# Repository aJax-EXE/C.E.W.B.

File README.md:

# C.E.W.B.: The Open Source Teaching Platform for Control Systems
**ECEN4620/MCEN4085: Senior Design Project - University of Colorado Boulder**  
**Sponsors:** Talles Santos  
&emsp;&emsp;&emsp;&emsp;&emsp; Nathan McNeil  
**Students:** [Alyssa Jackson](https://github.com/aJax-EXE) (Electrical and Computer Engineering)  
&emsp;&emsp;&emsp;&emsp;&emsp;Eric Pollert (Mechanical Engineering)  
&emsp;&emsp;&emsp;&emsp;&emsp;[Isaiah Knox](https://github.com/iknox001) (Mechanical Engineering)  

---

## Table of Contents
1. [Introduction](#introduction)
2. [Project Overview](#project-overview)
3. [System Specifications](#system-specifications)
4. [Repository Structure](#repository-structure)
5. [Hardware](#hardware)
   - [Circuit Design](#circuit-design)
   - [Data Transmission](#data-transmission)
   - [Accessory Storage](#accessory-storage)
   - [Device Deck](#device-deck)
   - [Motor Housing](#motor-housing)
   - [Electrical Compartment](#electrical-compartment)
   - [Attachments](#attachments)
6. [Software](#software)
   - [Dependencies](#dependencies)
   - [Arduino Code](#arduino-code)
   - [MATLAB/Simulink Interface](#matlabsimulink-interface)
   - [Custom Libraries](#custom-libraries)
7. [Getting Started](#getting-started)
   - [Hardware Setup](#hardware-setup)
   - [Software Setup](#software-setup)
   - [Running Your First Experiment](#running-your-first-experiment)
8. [Lab Experiments](#lab-experiments)
   - [Angular Position Control (Inertia Disc)](#angular-position-control-inertia-disc)
   - [Inverted Pendulum Balancing](#inverted-pendulum-balancing)
9. [Results](#results)
10. [Known Limitations](#known-limitations)
11. [Next Steps](#next-steps)
    - [List of Issues](#list-of-issues)
    - [After CEWB Functionality is Reached](#after-cewb-functionality-is-reached)
12. [Contributing](#contributing)
13. [License](#license)

---

*The CEWB, fully built*  
&emsp;

---

## Introduction

C.E.W.B. (name pending; referred to as 'CEWB' throughout this README) is a low-cost, open-source electromechanical teaching platform designed for teaching and applying control systems concepts in a real-world environment. It was developed as a direct functional replacement for the Quanser Qube-Servo 2, a $5,000 proprietary device that is now outdated and requires an older version of MATLAB to operate.

The device supports the same core laboratory experiments as the Qube-Servo 2, including angular position control with an inertia disc and inverted pendulum balancing. It is designed to be self-contained, portable, and fully compatible with MATLAB and Simulink.

All design files, code, and documentation are publicly available in this repository so that the device can be reproduced by any institution without reliance on proprietary hardware or software.

---

## Project Overview

This project set out to design a low-cost, open-source replacement for the Quanser Qube-Servo 2, a $5,000 device used in control systems classes. The target was a fully functional prototype delivered by May 2026 at under $1,000 per unit, capable of supporting the same lab experiments — including angular position control with an inertia disc and inverted pendulum balancing — while being self-contained, portable, and compatible with MATLAB/Simulink.

The design integrates all components into a Nanuk 905 protective case with built-in storage for attachments, cables, and the power supply. The system uses an Arduino microcontroller, a motor driver, and a custom PCB, with two interchangeable magnetic attachments — an inertia disc and a pendulum — mirroring the Qube-Servo 2's functionality. The projected per-unit production cost of $763.68 comes in well under the $1,000 target.

The device met most implementation requirements. Data transmission, MATLAB/Simulink compatibility, third-party manufacturability, self-contained storage, and transport protection all passed evaluation. Open-source documentation, including CAD files, a bill of materials, and assembly instructions, has been prepared and made publicly available.

However, the device did not fully replicate the closed-loop control performance of the Qube-Servo 2. The Arduino's data transmission rate is approximately an order of magnitude slower than the proprietary controller used in the Qube-Servo 2, causing significant control loop delays and excessive overshoot during inertia disc testing. As a result, the pendulum balancing test was not attempted.

The primary recommended next step is to replace the Arduino with a faster microcontroller, retest the system using the same control experiments, and proceed to a small production run once performance requirements are confirmed to be met.

---

## System Specifications

The following table lists the key performance parameters of the C.E.W.B. system alongside the Qube-Servo 2 equivalents for reference.

| Parameter | C.E.W.B. | Qube-Servo 2 |
|---|---|---|
| Motor | Maxon DC-max 26 S Ø26 mm | Maxon (discontinued) |
| Nominal input voltage | 24 V | 18 V |
| Nominal torque | 22.0 mN-m | 22.0 mN-m |
| Nominal speed | 3050 RPM | 3050 RPM |
| Encoder line count | 512 lines/rev | 512 lines/rev |
| Encoder resolution (quadrature) | 2048 counts/rev | 2048 counts/rev |
| Encoder resolution (deg) | 0.176 deg/count | 0.176 deg/count |
| Encoder resolution (rad) | 0.00307 rad/count | 0.00307 rad/count |
| Motor controller | Adafruit DRV8871 | PWM amplifier |
| Microcontroller | Arduino Uno R3 | Proprietary |
| Data transmission rate | ~50 Hz (USB serial) | ~500 Hz (proprietary) |
| Output voltage range | ±24 V | ±10 V (recommended) |
| Per-unit cost (production) | $763.68 | $5,000.00 |

---

## Repository Structure

```
C.E.W.B./
├── Datasheets/
│   ├── Electrical/                                # Datasheets for all electrical components
│   └── Hardware/                                  # Datasheets for hardware components
├── Documentation/                                # Documentation from the Senior Projects Class
├── Hardware/
│   ├── 3DModels/
│   │   ├── CurrentVersion/                       # Final production CAD files (SolidWorks)
│   │   │   ├── Device Components/                # All structural device parts
│   │   │   │   ├── Full Assembly.SLDASM
│   │   │   │   ├── Motor Arm.SLDASM
│   │   │   │   ├── Housing.SLDPRT
│   │   │   │   ├── Motor Plate.SLDPRT
│   │   │   │   ├── Motor Leg.SLDPRT
│   │   │   │   ├── Plate bend inlet.SLDPRT
│   │   │   │   ├── Inertia Disc.SLDPRT
│   │   │   │   ├── Attachment Interface.SLDPRT
│   │   │   │   ├── Pendulum Assembly.SLDASM
│   │   │   │   ├── Pendulum mount.SLDPRT
│   │   │   │   ├── Pendulum shaft.SLDPRT
│   │   │   │   ├── Pendulum Arm.SLDPRT
│   │   │   │   ├── Pendulum Stop.SLDPRT
│   │   │   │   ├── PCB.SLDPRT
│   │   │   │   ├── PCB Mounting Plate.SLDPRT
│   │   │   │   └── [purchased hardware SLDPRTs]
│   │   │   └── Storage Compartment Components/   # Lid storage assembly parts
│   │   │       ├── Foam_Panel.SLDPRT
│   │   │       ├── Front Panel.SLDPRT
│   │   │       └── Rear Lid Panel.SLDPRT
│   │   └── PastVersions/                         # Design iteration history
│   └── PCBModels/
│       ├── ArduinoShieldDesign/                  # KiCad PCB design files
│       │   ├── ForwardDesign/                    # Current production PCB
│       │   ├── ReverseDesign/                    # Earlier PCB iteration
│       │   ├── OldTestBoard/                     # First test board
│       │   └── PotentialFix/                     # Proposed PCB fix iteration
│       ├── GerberFiles/
│       │   ├── ForwardFiles/                     # Gerber files for production PCB
│           └── ReverseFiles/                     # Gerber files for reverse design
├── Images/                                       # Images used in this README and in the documentation
├── Software/
│   ├── Libraries/                                # Arduino libraries — install these manually
│   │   ├── CombiningEncoderCounts/               # CEWBEncoder source
│   │   │   ├── CEWBEncoder.cpp
│   │   │   └── CEWBEncoder.h
│   │   └── OtherFunctions/                       # CEWBFunctions source
│   │       ├── CEWBFunctions.cpp
│   │       └── CEWBFunctions.h
│   ├── ExamplesAndTests/
│   │   ├── ArduinoTests/                         # Standalone Arduino diagnostic sketches
│   │   │   ├── CalcToAnalogVal/                  # PWM value calculator
│   │   │   ├── CommunicationConstantlySendingData/  # Serial format test
│   │   │   ├── EncoderQuadTest/                  # Encoder wiring verification
│   │   │   ├── InterruptEncoderTest/             # Interrupt-based encoder test
│   │   │   └── MotorRampSpeedTest/               # Motor driver verification
│   │   ├── ProofOfConcept/                       # Early proof-of-concept scripts
│   │   └── SimulinkTests/                        # Simulink integration test models
│   │       ├── BasicSimulinkCommunication/       # Initial serial block example
│   │       ├── BypassSerialBlockSimulinkConnectionTest/
│   │       ├── CompleteSimulinkRunTest/
│   │       │   ├── BasicRunning/                 # Open-loop voltage test model
│   │       │   └── WorkingModel/                 # ⭐ Main working model
│   │       │       ├── ArduinoSerial.m           # MATLAB System block
│   │       │       ├── WorkingModel.ino          # Arduino sketch
│   │       │       └── PIDController.slx         # Simulink model
│   │       ├── SimulinkFormattingTest/
│   │       └── SimulinkReadEncoder/              # Encoder-only read test
│   ├── SendingBytesTest/                         # Binary byte transmission experiment
│   ├── SimulinkReadWriteSerialPort/              # Early serial block experiments
│   ├── SpinMotorWithSimulinkTest/                # Motor spin test
│   └── UpgradedMotorWSimulinkTest/               # Updated motor test
├── .gitignore
└── README.md
```
 
> ⭐ **For most users, the only files needed are in `Software/ExamplesAndTests/SimulinkTests/CompleteSimulinkRunTest/WorkingModel/`** — the Arduino sketch, MATLAB System block, and Simulink model are all there.
---

## Hardware

&emsp;
  
*3D models of the CEWB and its parts*  
&emsp;

### Circuit Design

*The CEWB electrical schematic*  
&emsp;

*The CEWB PCB model*  
&emsp;

The electrical system is built around an Arduino Uno R3 microcontroller and an Adafruit DRV8871 motor driver, both connected through a custom PCB. The PCB acts as a junction point between the motor, encoders, and microcontroller, consolidating all wiring and reducing the risk of loose connections. A 24V Mean Well GST90A24-P1M power supply provides power to the system via a front-panel power port. A front-panel USB-B port connects the Arduino to the user's laptop for data transmission.

The PCB is insulated from the aluminum mounting panel using an acrylic backing plate to prevent electrical interference.

### Data Transmission

Communication between the Arduino and MATLAB/Simulink is handled over USB serial at 115200 baud using a custom request/response packet protocol. Simulink sends a scaled integer voltage command, and the Arduino responds with the current encoder count and applied voltage. The full protocol is described in the [Arduino Code](#arduino-code) section of the Software documentation.

### Accessory Storage

*The storage lid that houses the CEWB attachments*  
&emsp;

The accessory storage compartment is made up of two pieces of hardboard and one piece of foam with cutouts for the accessories to fit into. The rear panel of hardboard has magnets glued into it, which allow the attachments to be secured in their respective locations during storage. Hardboard was selected for the front and rear panels as it is a light, cheap, and sturdy material. Foam was chosen for the middle panel as it is low-density and fills the space between the boards without significantly increasing weight. The three panels are glued together with super glue and are fixed into the top of the Nanuk 905 case using thread-forming screws.

### Device Deck

The main part of the deck of the device is a bent piece of aluminum sheet metal which is screwed into the Nanuk 905 case using thread-forming screws and serves as a mounting plate for the rest of the components. This part is bent to create a compartment for storing the power supply and the data transmission cable. The top surface of this panel has two ports: a USB port where the data transmission cable is plugged in, and a power port where the device is connected to the power supply. The ports were added to clean up the visual appearance of the device and remove the need for cables to be plugged directly into the electrical compartment. On the right side of the panel there is a cavity with a U-shaped bent piece of aluminum sheet metal mounted to the bottom of the panel, which serves both as a mounting location for the motor housing and as a barrier between the user and the internal components. The cavity allows the motor housing to fold into the device when stored. The trough contains a hole to allow wires to pass through between the motor housing and the electrical compartment. This hole is lined with a silicone grommet which protects the wires from fraying when the motor housing is moved between its storage and operating positions.

### Motor Housing

The motor housing consists of three main structural components, all made from aluminum sheet metal. The two motor housing legs give the housing the height required for the pendulum attachment and serve as the mounting location for the hinge, which allows the housing to pivot between its operational and storage positions. The hinge consists of a partially threaded socket head screw, nuts, and nylon washers. The partially threaded screw was chosen to provide a smooth surface for the hinge to rotate on. The nylon washers secure the housing in place during operation while still allowing rotation under sufficient force to slightly deform the nylon. The two washers at the end are jammed together to secure the hinge at a calibrated tightness, ensuring the hinge can be rotated but remains secured during operation.

The third structural component is the motor mounting plate, which features a bend that serves as a handle when switching the device between positions. This plate is attached at the top of the two motor legs using bolts and locknuts, and has the motor mounted to its underside using machine screws secured directly into threaded holes in the top of the motor. The motor is from Maxon and was chosen to replicate the motor of the Qube-Servo 2 as closely as possible given that the original motor is no longer available. An optical encoder is mounted to the rear axle of the motor using double-sided adhesive, which allows the encoder to be secured firmly without screws, as there are no mounting locations on the rear of the motor. The attachment interface is a small machined aluminum disc mounted to the end of the top motor shaft using a set screw. This component has magnets that allow the attachments to be fixed to the motor shaft during use. The motor plate also has a small 3D-printed elbow-shaped component mounted near the motor, which serves as a stop to prevent the pendulum from over-rotating and damaging its wiring. The mounting plate also has a 3.5 mm jack port for connecting the encoder from the pendulum attachment during use.

### Electrical Compartment

*The CEWB electrical compartment*  
&emsp;

The electrical compartment is located between the bend in the top panel of the device deck and the trough. The electrical components — including the motor driver, Arduino, and PCB — are mounted to the backside of the panel using nuts and bolts, with a piece of acrylic sized to match the PCB placed behind it to insulate the exposed circuitry from the aluminum panel and prevent electrical interference.

### Attachments

The two attachments are the inertia disc and the pendulum. The inertia disc is a machined aluminum disc which adds rotational inertia to the motor shaft for use in position control experiments. The disc has lines engraved into its top surface which allow the user to visually track the motor's position and verify control system behavior. The disc has four magnets on the back which allow it to be secured to the attachment interface during use and to the attachment storage compartment when stored.

The pendulum consists of three machined components. The pendulum cylinder is machined from aluminum and is the mounting location for the pendulum assembly. It has magnets on one side for mounting to the attachment interface and storage compartment, and two bearings press-fit into its internal bore which allow the pendulum axle to rotate freely. The pendulum axle is made from steel and is inserted through the two bearings and secured using two retaining rings that fit into grooves in the axle positioned to press against the bearings. An optical encoder is attached to the pendulum cylinder using machine screws and tracks the angular position of the axle during pendulum experiments. The encoder connects via a 3.5 mm cable to a jack on the motor mounting plate, allowing encoder data to be transmitted to the electrical compartment. The pendulum arm is mounted on the far end of the axle using a set screw and acts as a counterweight to create the tipping moment that the control system must compensate for in the inverted pendulum experiment.

---

## Software

### Dependencies

**Arduino IDE (1.8.x recommended)**
- CEWBEncoder (included in `Software/MATLAB/Libraries/CEWBEncoder/`)
- CEWBFunctions (included in `Software/MATLAB/Libraries/CEWBFunctions/`)

**MATLAB/Simulink**
- MATLAB R2024b or later
- Simulink
- No additional toolboxes required — serial communication is handled via a custom `matlab.System` object

### Arduino Code

The main Arduino sketch (`WorkingModel.ino`) implements a simple request/response serial protocol. Simulink sends a voltage command, the Arduino executes it on the motor, and responds with the current encoder count and applied voltage.

**Packet format:**

| Direction | Format | Example |
|---|---|---|
| Simulink → Arduino | `#sXXXXXX\n` | `#+037500\n` (3.75V × 10000) |
| Arduino → Simulink | `#sXXXXXX,sXXXXXX\n` | `#+000512,+037500\n` |

Voltage is transmitted as a scaled integer (real volts × 10000) to preserve 4 decimal places without transmitting a decimal point. Conversion is handled by `makeVoltage()` in CEWBFunctions.

The Arduino also implements a **500ms watchdog** — if no packet is received within 500ms (e.g. if Simulink is stopped or the USB cable is disconnected), the motor is cut automatically.

### MATLAB/Simulink Interface

Communication between Simulink and the Arduino is handled by `ArduinoSerial.m`, a `matlab.System` subclass that runs a 200Hz background timer independently of the Simulink step rate. This decouples serial timing from Simulink's solver, allowing smoother encoder data with less blocking.

**Block interface:**

| Port | Direction | Description |
|---|---|---|
| `v_in` | Input | Voltage command (−6 to +6 V) |
| `enc_out` | Output | Raw encoder count |
| `v_out` | Output | Voltage currently applied (for scope) |

**Configurable block parameters (set by double-clicking the block):**

| Parameter | Default | Description |
|---|---|---|
| `COMPort` | `/dev/ttyACM0` | Serial port (Linux) or `COM3` (Windows) |
| `BaudRate` | `115200` | Serial baud rate |
| `TimerPeriod` | `0.005` | Background timer period in seconds (0.005 = 200Hz) |

To convert `enc_out` to angle, wire it through a Gain block set to `(2*pi)/2048` for radians or `360/2048` for degrees.

### Custom Libraries

**CEWBEncoder**  
Interrupt-driven quadrature encoder library supporting ENC1X, ENC2X, and ENC4X decoding modes using Arduino pin change interrupts (PCINT). Supports up to 8 encoders simultaneously.

Key functions:
```cpp
CEWBEncoder enc(pinA, pinB, ENC4X);  // constructor
enc.begin();                          // enable interrupts
enc.getCount();                       // returns long count
enc.getDirection();                   // returns -1, 0, or 1
enc.resetCount();                     // resets count to zero
```

**CEWBFunctions**  
Utility functions for motor voltage conversion.

Key functions:
```cpp
voltToPWM(float voltage);   // converts voltage magnitude to PWM (0-255)
PWMToVolt(uint8_t PWM);     // converts PWM back to voltage
makeVoltage(long value);    // descales integer (value / 10000.0) to float volts
```

Note: `voltToPWM` maps voltage against a 24V maximum (`maxVolt = 24`). Passing values above 24V returns 255. Always pass `fabsf(voltage)` — direction is handled separately by `spinMotor`.

---

## Getting Started

### Hardware Setup

1. Connect the USB-B cable from the device's front panel USB port to your laptop.
2. Connect the power cable to the device's front panel power port and plug it into the wall.
3. Raise the motor housing to its upright operating position.
4. Attach the desired attachment (inertia disc or pendulum) to the motor interface magnetically.
5. If using the pendulum attachment, plug the 3.5 mm encoder cable into the jack on the motor plate.

> ⚠️ **Before use, ensure the motor housing is in the upright position and that power and computer cables — along with any other objects — are clear of the motor shaft.**

### Software Setup

**Arduino:**
1. Install Arduino IDE 1.8.x.
2. Copy `CEWBEncoder` and `CEWBFunctions` folders from `Software/MATLAB/Libraries/` into your Arduino libraries directory:
   - Linux (Snap): `~/snap/arduino/85/Arduino/libraries/`
   - Linux (AppImage/standard): `~/Arduino/libraries/`
   - Windows: `Documents/Arduino/libraries/`
3. Open `Software/Arduino/WorkingModel/WorkingModel.ino` in Arduino IDE.
4. Select **Tools → Board → Arduino Uno** and the correct port under **Tools → Port**.
5. Upload the sketch.

**MATLAB/Simulink:**
1. Place `ArduinoSerial.m` in the same folder as your Simulink `.slx` model file — Simulink looks for it by name in the current working directory.
2. Open your Simulink model.
3. Add a **MATLAB System** block (Simulink → User-Defined Functions → MATLAB System).
4. Double-click the block and select `ArduinoSerial` from the dropdown.

> ⚠️ **If `ArduinoSerial` does not appear in the dropdown, the `.m` file is not in the same folder as your Simulink model. Move it and try again.**

5. Set `COMPort` to match your Arduino's port (check Arduino IDE → Tools → Port).
6. Set the Simulink solver to **Fixed-step**, step size `0.02` (Ctrl+E → Solver).
7. Press **Play** — the block handles serial port opening, the background timer, and cleanup automatically.

### Running Your First Experiment

*The block diagram of the first example experiment*  
&emsp;

A simple open-loop voltage test:
1. Add a **Signal Generator** block (square wave, amplitude 3, frequency 0.5 Hz).
2. Wire it to `v_in` on the ArduinoSerial block.
3. Add a **Gain** block after `enc_out` with value `360/2048` to convert counts to degrees.
4. Connect both the Gain output and `v_out` to a **Scope** block.
5. Press **Play**. The motor should respond to the square wave and the scope should display the angular position and applied voltage.

---

## Lab Experiments

### Angular Position Control (Inertia Disc)

**Objective:** Command the inertia disc to move between angular positions (e.g. +1 rad and −1 rad) while minimizing overshoot using a PID controller.

**Simulink wiring:**
```
Constant (setpoint, rad) ──► Sum(+−) ──► PID ──► Saturation(±6V) ──► v_in ──► ArduinoSerial
                                ▲                                                      │
                                └──────────── Gain(2π/2048) ◄──── enc_out ────────────┘
```

**Recommended starting PID gains:**

| Gain | Starting Value |
|---|---|
| Kp | 0.1 |
| Ki | 0.0 |
| Kd | 0.1 (use filtered derivative: `10s/(s+10)`) |

> **Important:** Do not use Simulink's built-in `Derivative` block — it has infinite gain at high frequencies and will amplify serial timing noise, causing unstable motor behavior. Use a `Transfer Fcn` block with numerator `[10 0]` and denominator `[1 10]` instead.

**Note:** Due to the Arduino's ~20ms serial round-trip latency, aggressive PID gains will cause instability. Start with a low Kp and no derivative term, then increase gradually.

### Inverted Pendulum Balancing

> **Status: Not yet validated.** The inverted pendulum experiment requires faster closed-loop performance than the current Arduino-based system can reliably provide. This experiment is planned for a future hardware revision using a faster microcontroller. See [Next Steps](#next-steps).

---

## Results

The device met the following design requirements:

| Requirement | Target | Result |
|---|---|---|
| Accurate data transmission | Pass | ✅ Pass |
| MATLAB/Simulink compatibility | Pass | ✅ Pass |
| Cost target | < $1,000 | ✅ $763.68 |
| Self-contained storage | Pass | ✅ Pass |
| Transport protection | Pass | ✅ Pass (Nanuk 905, ASTM D-4169 DC-18 certified) |
| Third-party manufacturability | Pass | ✅ Pass |
| Software updatability | Pass | ✅ Pass (on supported MATLAB versions) |
| Qube function replication | Pass | ❌ Partial — inertia disc overshoot; pendulum not attempted |
| Motor and encoder performance | Comparable | ❌ Not met under closed-loop conditions |

---

## Known Limitations
**Serial latency (~20ms round-trip)**  
The Arduino Uno communicates over USB serial at approximately 50Hz, compared to the Qube-Servo 2's ~500Hz proprietary interface. This introduces significant control loop delay, causing excessive overshoot at higher PID gains. The background timer in `ArduinoSerial.m` partially mitigates this by running at 200Hz independently of Simulink, but the underlying serial round-trip remains the bottleneck.

**Encoder noise at high motor speeds**  
At high voltages, motor vibration can introduce noise on the encoder signal lines, causing occasional miscounts. Adding 10–100nF ceramic capacitors between each encoder signal pin and GND reduces this significantly.

**`voltToPWM` maps against 24V maximum**  
The `voltToPWM` function in CEWBFunctions maps input voltage against a 24V maximum. Voltages in the recommended ±6V operating range use only 25% of the available PWM range. If finer motor resolution is needed, change `maxVolt` in `CEWBFunctions.cpp` to match your intended operating voltage range.

---

## Next Steps

### List of Issues

In order to address the fundamental limitations of the CEWB and improve it in future iterations, the following items should be investigated:

- **Research faster microcontrollers**  
  The Arduino Uno R3 is not powerful enough to spin the motor, count the encoder position, and transmit/receive data to and from Simulink accurately in real time. To improve throughput and reduce computational bottlenecks, consider:
  - Using a single faster microcontroller (Raspberry Pi Pico, STM32, Teensy 4.x, etc.)
  - Using two or more microcontrollers with divided responsibilities — e.g. one handling motor control and encoder counting while another manages data transmission

- **Switch data transmission from strings to bytes**  
  The current string-based packet format is human-readable and useful for debugging, but binary byte transmission is significantly faster. The string format should be retained as a diagnostic/test option, but the production firmware should use binary packets.

- **Research higher-rate data transmission methods**  
  The Arduino Uno communicates at approximately 50Hz while the Qube-Servo 2 operates at ~500Hz. Investigate how the Qube-Servo 2 achieves this rate and identify equivalent approaches for the CEWB.

- **Look into wireless encoders for the inverted pendulum**  
  With the current setup, the pendulum attachment cannot rotate continuously 360° because of the wire connecting to the audio jack port on the motor plate. While this is sufficient for balancing at 180°, a wireless encoder connection would eliminate the rotation constraint and enable more complex experiments.

- **Add a strap to secure the inverted pendulum attachment in storage**  
  Currently, the pendulum shaft falls out of its storage cutout and props the lid open, preventing it from closing. A simple retaining strap would resolve this without requiring significant redesign.

- **Develop additional inertia disc variants**  
  Additional discs of different masses and radii would provide a wider range of system dynamics, enriching the experiments that can be demonstrated and taught.

- **Combine the `CEWBEncoder` and `CEWBFunctions` libraries**  
  Consolidating both libraries into a single library would not improve performance but would simplify installation and make the codebase easier for users to navigate.

- **Refine 3D models**  
  Minor dimensional discrepancies have been observed in received parts. While all parts are functional, tighter tolerances and updated models would reduce the need for post-receipt modification.

- **Document fabrication vendors and order specifications**  
  For the project to scale to wider adoption, the specific vendors used and the exact order specifications (dimensions, material, finish, etc.) for each custom part should be documented in the repository.

- **Investigate current surge protection**  
  If the motor stalls, current can spike and potentially damage other electrical components. Additional protection circuitry beyond the motor driver's built-in limiting should be explored.

- **Finalize the C.E.W.B. name**  
  The name was conceived to copy the Qube's spelling but does not currently stand for anything. A meaningful acronym or a new name entirely should be decided upon before wider release.

- **Research ways to make the motor run quieter**  
    The motor constantly emits a low and piercing buzz that can cause headaches. Look into making that stop and run quiet like the Qube does.

### After CEWB Functionality is Reached

Once the CEWB achieves reliable closed-loop performance, the following steps are planned:
1. Retest angular position control with the inertia disc using the same PID experiments
2. Attempt and validate inverted pendulum balancing
3. Assemble a small production run for deployment in the control systems course
4. Provide a prototype unit to the course instructor for curriculum integration

---

## Contributing

This project is open-source and contributions are welcome. To contribute:

1. Fork the repository
2. Create a feature branch (`git checkout -b feature/your-feature`)
3. Commit your changes (`git commit -m 'Add your feature'`)
4. Push to the branch (`git push origin feature/your-feature`)
5. Open a pull request

For questions or technical support, contact:
- **Dr. Talles Santos** (project sponsor): Talles.Santos@colorado.edu
- **Dr. Nathan McNeil** (project sponsor): Nathan.Mcneil@colorado.edu
- **Alyssa Jackson** (project member): alyssajackson436@gmail.com
- **US Digital** (encoders): support@usdigital.com | 800-736-0194
- **Maxon Motors**: info.us@maxongroup.com | (508) 677-0520

---

## License

This project is open-source. All CAD files, code, and documentation are made publicly available for reproduction and modification. See the repository for license details.

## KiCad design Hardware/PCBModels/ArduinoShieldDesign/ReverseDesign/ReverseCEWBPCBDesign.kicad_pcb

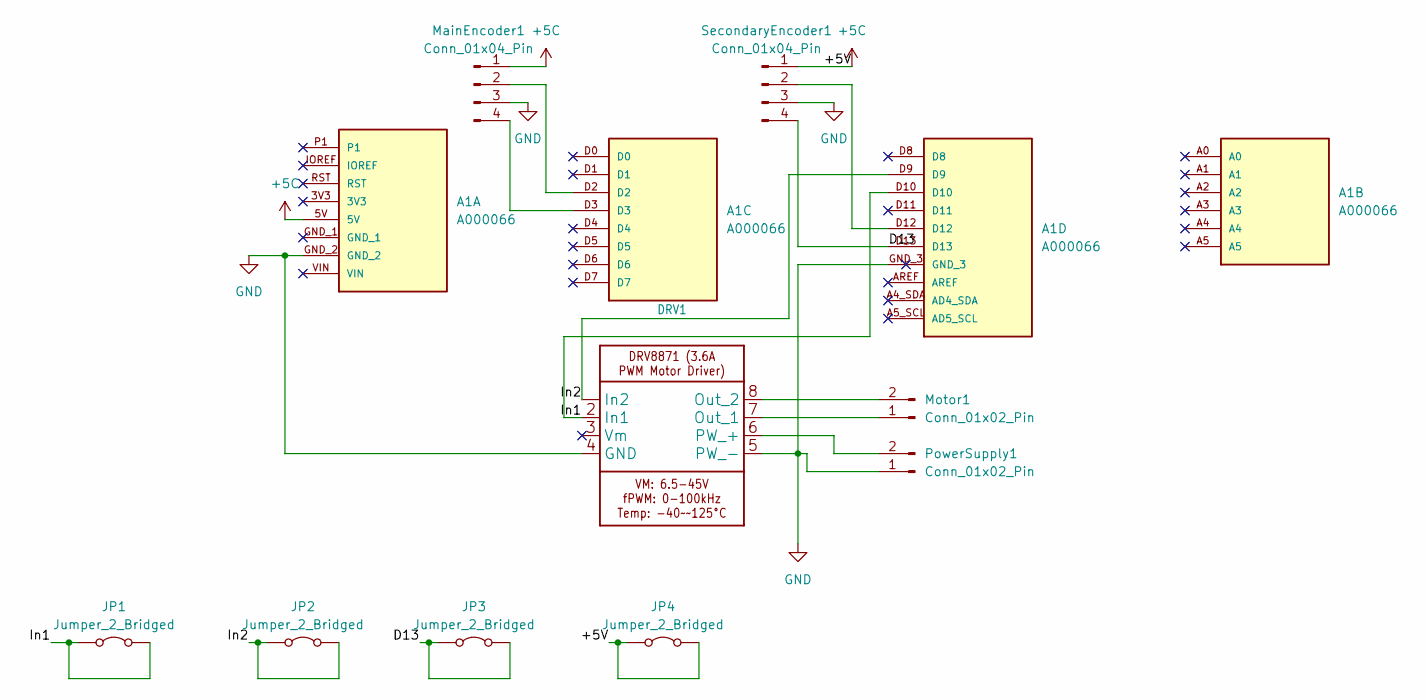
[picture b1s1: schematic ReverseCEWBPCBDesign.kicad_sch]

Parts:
A1: A000066; ARDUINO_A000066
DRV1: DRV8871_manual
JP1, JP2: Jumper_2_Bridged; R_Axial_DIN0207_L6.3mm_D2.5mm_P15.24mm_Horizontal
JP3, JP4: Jumper_2_Bridged; R_Axial_DIN0204_L3.6mm_D1.6mm_P5.08mm_Horizontal
MainEncoder1: Conn_01x04_Pin; PinHeader_1x04_P2.54mm_Vertical
Motor1: Conn_01x02_Pin; PinHeader_1x02_P2.54mm_Horizontal
PowerSupply1: Conn_01x02_Pin; PinHeader_1x02_P2.54mm_Horizontal
SecondaryEncoder1: Conn_01x04_Pin; PinHeader_1x04_P2.54mm_Vertical

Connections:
+5C: A1.5V, JP4.1 (A), JP4.2 (B), MainEncoder1.1, SecondaryEncoder1.1
/D13: A1.D13, JP3.1 (A), JP3.2 (B), SecondaryEncoder1.4
/In1: A1.D10, DRV1.2 (In1), JP1.1 (A), JP1.2 (B)
/In2: A1.D9, DRV1.1 (In2), JP2.1 (A), JP2.2 (B)
GND: A1.GND_2, A1.GND_3, DRV1.4 (GND), DRV1.5 (PW_-), MainEncoder1.3, PowerSupply1.1, SecondaryEncoder1.3
unnamed: DRV1.7 (Out_1), Motor1.1
unnamed: DRV1.8 (Out_2), Motor1.2
unnamed: DRV1.6 (PW_+), PowerSupply1.2
unnamed: A1.D2, MainEncoder1.2
unnamed: A1.D3, MainEncoder1.4
unnamed: A1.D12, SecondaryEncoder1.2

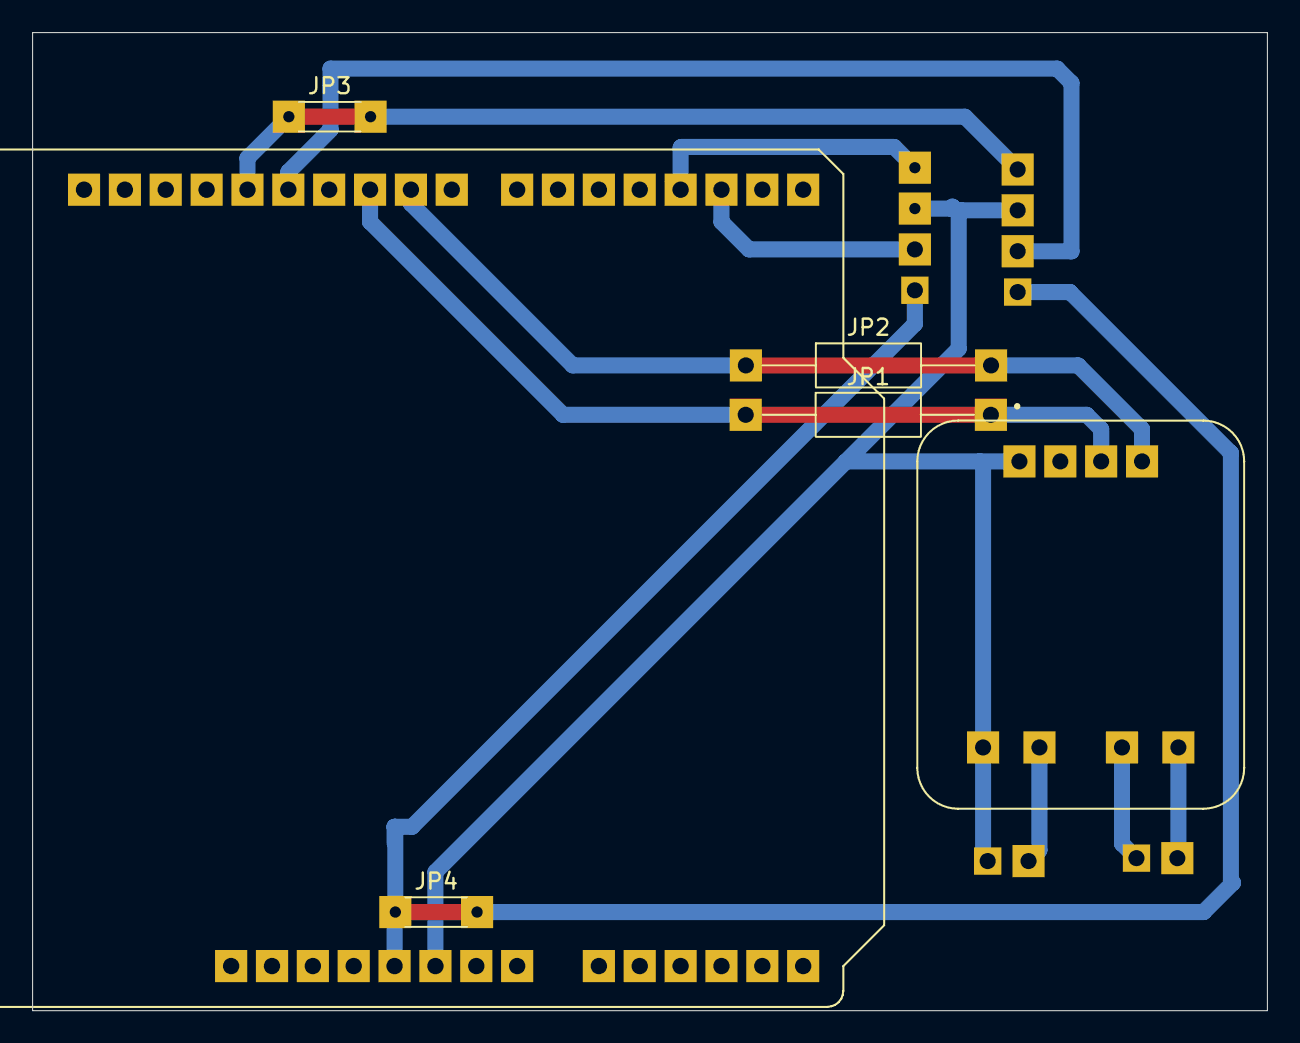
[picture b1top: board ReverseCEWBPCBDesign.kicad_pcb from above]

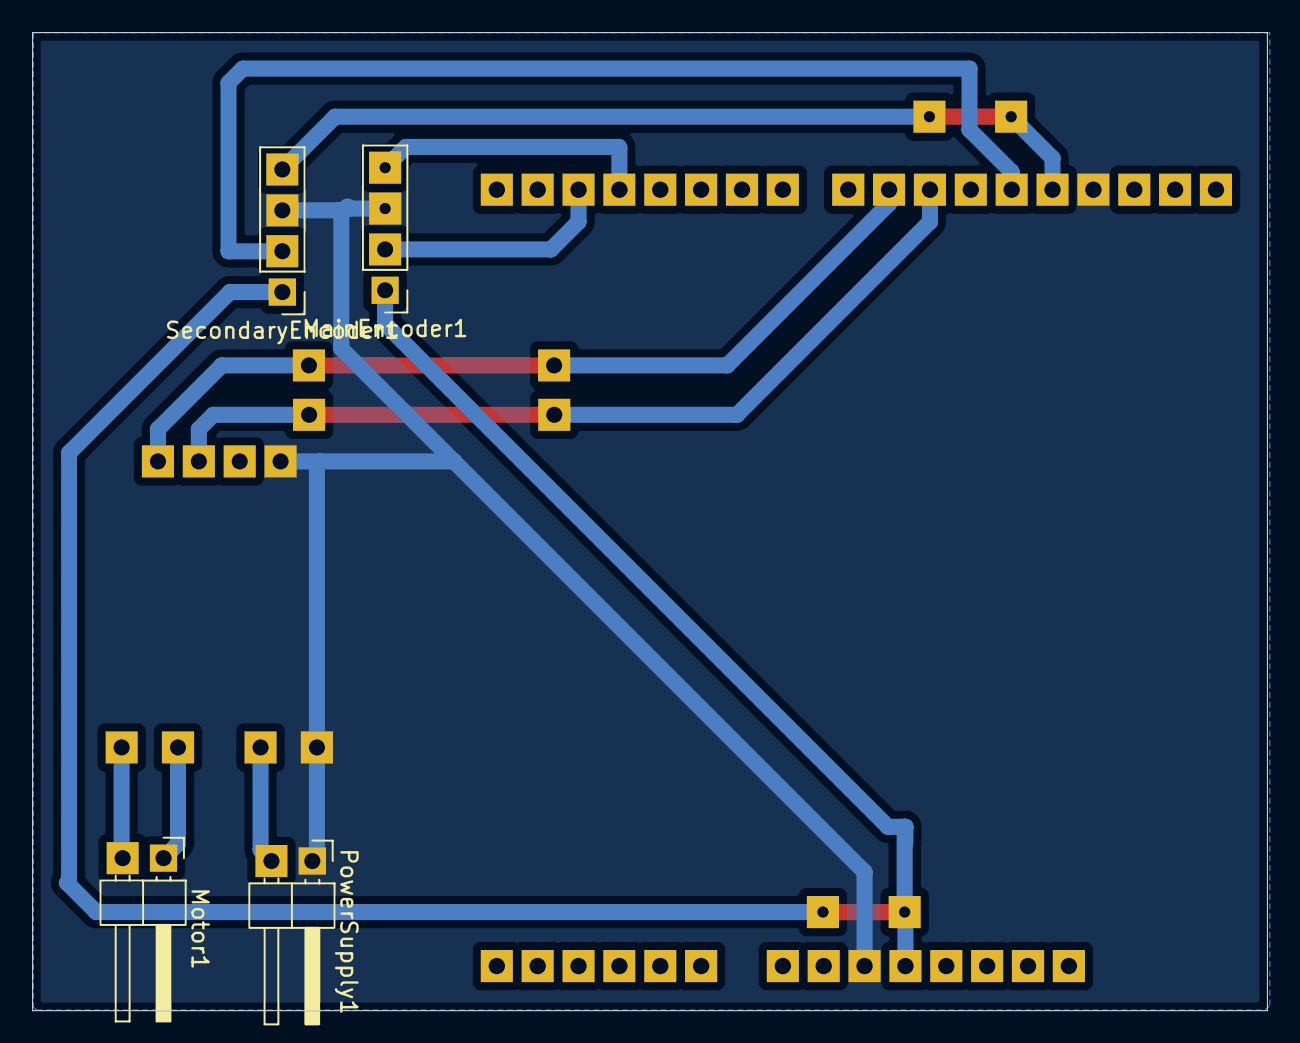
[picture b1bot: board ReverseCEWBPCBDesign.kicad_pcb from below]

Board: 2 copper layers, 76.8 x 60.8 mm, 10 parts (4 on the bottom side), 11 nets.

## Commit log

2025-09-09 starting point
2025-09-10 testing
2025-09-15 Arduino Encoder Works, but acts funny?
2025-09-30 Test w/o Libraries
2025-09-30 added
2025-11-03 Arduino to C++ Test Begin
2025-11-10 current progress
2025-11-10 More Testing Needed
2025-11-11 MotorRunningwEncoderCounter
2025-11-13 More Testing Writing from Txt to Arduino Start
2025-11-17 Syncing Current Progress to Github
2025-11-30 MoreStuff
2025-12-01 Added the Circuit Diagram
2025-12-02 Testing Code Pretty Much Done
2025-12-05 Some cleaning
2025-12-06 Fixes
2025-12-07 Temp fix for now
2026-01-06 Current progress up to date
2026-01-27 LibraryProgress
2026-01-30 Small update
2026-01-31 Starting the parsing; finished with formatting
2026-02-01 Finished the parsing code; working on the formatting code again
2026-02-02 Reworking the formatting and parsing
2026-02-03 Some updates
2026-02-03 The library is complete
2026-02-04 Slight library update
2026-02-06 Taking data from the arduino and putting it to the terminal and text file
2026-02-08 CFormatting Finished
2026-02-09 Progress on Libraries, and serial to text file data transfer
2026-02-09 More serial to text updates and some cleaning up
2026-02-19 Putting all the tests together
2026-02-20 Centralizing the Software stuff and Starting the PCB Design
2026-02-20 More cleaning and setting up for 3d models to be added
2026-02-20 SimulinkReadWriteSerialPort implementation
2026-02-24 KiCAD. Arduino and Driver models.
2026-02-25 Working on the PCB Design and an updated Encoder count
2026-02-25 PCB example.
2026-02-26 Updated PCB Design and Schematic
2026-02-26 Updated Final Gerber Files for the PCB
2026-03-01 Minor brd modification and Generate FlatCam files.
2026-03-02 Uploading the files from the 3d model
2026-03-04 Adding photos and testing the simulink diagrams
2026-03-04 Updated PCB Design
2026-03-04 New board - Generate FlatCam files.
2026-03-04 Final PCB Update (For Now)
2026-03-09 Encoder Library Updated to work with 1x, 2x, and 4x all in one
2026-03-11 Create Past Versions
    All past 3D models of the design itterations of the device
2026-03-11 Create PastVersions
2026-03-11 New Files
2026-03-11 Fun Update
2026-03-11 Rename Hardware/3DModels/57155K323_Stainless Steel Ball Bearing.SLDPRT to Hardware/3DModels/Prototype2/57155K323_Stainless Steel Ball Bearing.SLDPRT
2026-03-11 Rename Hardware/3DModels/Prototype2/57155K323_Stainless Steel Ball Bearing.SLDPRT to Hardware/3DModels/PastFiles/Prototype2/57155K323_Stainless Steel Ball Bearing.SLDPRT
2026-03-11 Rename Hardware/3DModels/Assun Motor.SLDPRT to Hardware/3DModels/PastFiles/Prototype2/Assun Motor.SLDPRT
2026-03-11 Rename 57155K323_Stainless Steel Ball Bearing.SLDPRT to 57155K323_Stainless Steel Ball Bearing.SLDPRT
2026-03-11 Rename Assun Motor.SLDPRT to Assun Motor.SLDPRT
2026-03-11 Rename Hardware/3DModels/Case_inner_surface.SLDPRT to Hardware/3DModels/PastVersions/Prototype2/Case_inner_surface.SLDPRT
2026-03-11 Rename Hardware/3DModels/Full Assembly.SLDASM to Hardware/3DModels/PastVersions/Prototype2/Full Assembly.SLDASM
2026-03-11 Rename Hardware/3DModels/Housing.SLDPRT to Hardware/3DModels/PastVersions/Prototype2/Housing.SLDPRT
2026-03-11 Rename Hardware/3DModels/Inertia Disc.SLDPRT to Hardware/3DModels/PastVersions/Prototype2/Inertia Disc.SLDPRT
2026-03-11 Rename Hardware/3DModels/Maxon Motor.SLDPRT to Hardware/3DModels/PastVersions/Prototype2/Maxon Motor.SLDPRT
2026-03-11 Rename Hardware/3DModels/Motor Arm.SLDASM to Hardware/3DModels/PastVersions/Prototype2/Motor Arm.SLDASM
2026-03-17 Basic Simulink Connection to Arduino Made and Updated PCB Models for different Arduino Board Configurations
2026-03-17 Start of Cleaning
2026-03-22 Testing with Byte Sending instead of String Sending
2026-03-25 New milling and drilling files - Generate FlatCam files.
2026-03-26 Added the pcb for the test circuit and cleaned up some code
2026-03-27 NewEncoderTest
2026-03-27 Updated Simulink Test
2026-03-27 Added the old version of the simulink model
2026-03-27 More old simulink versions
2026-03-27 Library Folders
2026-03-30 Added a Solidworks PCB Model and Testing Simulink Connection Speed
2026-04-01 Simulink Update and pcb check
2026-04-01 Testing from new computer
2026-04-01 Test concluded
2026-04-02 A New Simulink Connection Approach, working out the kinks
2026-04-02 Simulink Now Runs in Real Time, plus having the old stuff here for difference shown
2026-04-04 Upgrade to the Functions Library and some testing to the simulink connection
2026-04-06 Start of Testing
2026-04-07 Simulink Qube Tests Added and some Cleaning Done
2026-04-22 Reorganization and cleaning
2026-04-22 More cleaning
2026-04-22 Adding Images and Cleaning up
2026-04-28 Accurate Encoder counting and trying out different solutions to the problem
2026-05-01 Proof of Concept simulation, PID attempts, and some cleaning
2026-05-04 Updating the testing files
2026-05-04 3D model moving
2026-05-04 Added Images
2026-05-04 Addedd Datasheets
2026-05-06 Images added and README started
2026-05-06 Fixing the spacing
2026-05-06 Conflict fixed
2026-05-08 Getting started and added links to accounts
2026-05-11 Sections of the README and new image
2026-05-11 Update README.md
    Added mechanical hardware components section
2026-05-14 Added and sorted Datasheets, added reports and instructions, working on README, and added images
2026-05-15 README progress
2026-05-15 Mostly complete README; fix table of contents and respo structure
2026-05-15 Added images and improved README; still need some fixes
2026-05-15 Finally completed README
2026-05-15 Create LICENSE
